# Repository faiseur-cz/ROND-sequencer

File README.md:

WARNING : It has been reported on modwiggler that this circuit is NOT OK!!! So please, check the forum. There were some solutions given. 
Right now i will not take the time needed to redo everything, because it would need some global redesign, and this project is not a priority for me.
Feel free to do it and write me directly or on the forum, it would be great!

Original description :
I finished the design and built a couple of them, all works as it should. So you can use the gerbers to make your own version.

There is a thread on modwiggler if you have any question :
https://modwiggler.com/forum/viewtopic.php?t=284588

ROND is an 8 step analog sequencer, kind of augmented (and circular!) baby8

- Pattern length rotary switch to set the number of steps in your sequence
- You can choose between two levels of CV (5v/2.5v), if you need more or less precision in the tuning of each step.
- Gates on/off for each step, on the right of the module.
- Run/Tune switch and Next Step push-button to facilitate tuning

CALIBRATION PROCEDURE :
- set the Run/Tune switch in TUNE position
- make sure the selected gate switch is ON (high position) and the corresponding pot is fully clockwise (maximum CV)
- monitor the CV output voltage and turn the trimpots until you reach precisely 5V (with the switch in 5V position) and 2.5V (with the switch in 2.5V position)
- DONE!

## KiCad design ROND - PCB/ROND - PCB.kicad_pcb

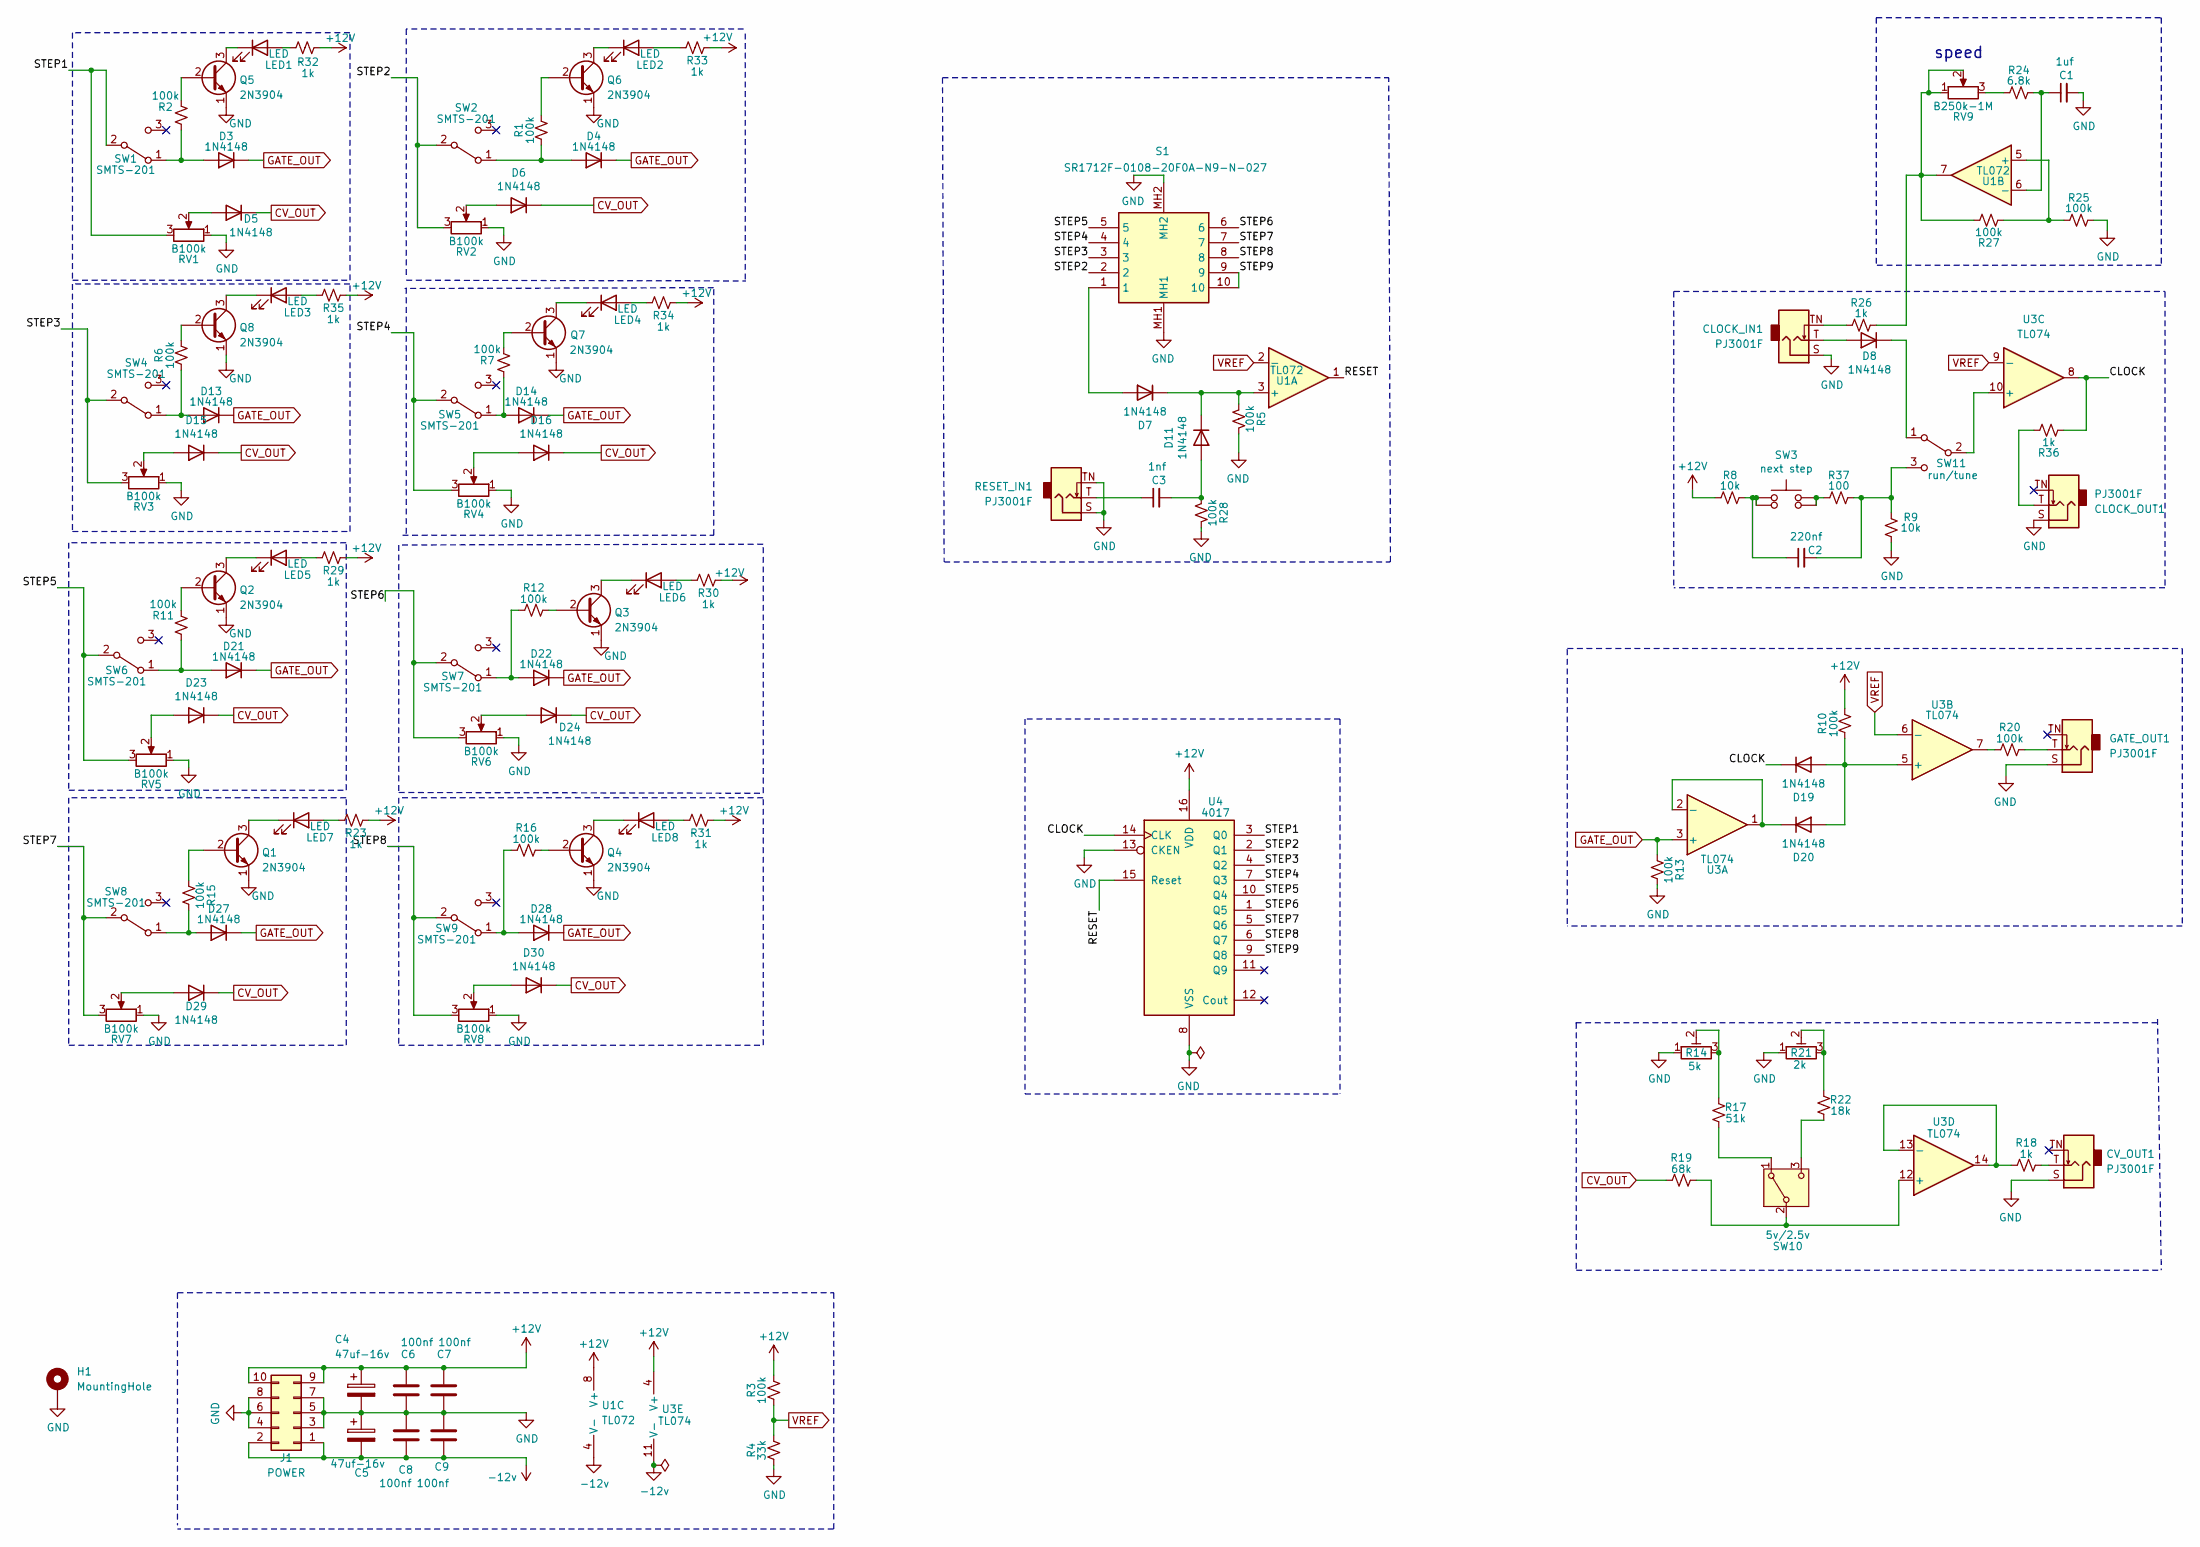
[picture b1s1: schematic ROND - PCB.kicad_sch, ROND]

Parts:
C1: 1uf; C_Rect_L7.2mm_W3.5mm_P5.00mm_FKS2_FKP2_MKS2_MKP2
C2: 220nf; C_Disc_D5.0mm_W2.5mm_P5.00mm
C3: 1nf; C_Rect_L7.2mm_W3.5mm_P5.00mm_FKS2_FKP2_MKS2_MKP2
C4, C5: 47uf-16v; CP_Radial_D5.0mm_P2.00mm
C6, C7, C8, C9: 100nf; C_Disc_D3.0mm_W2.0mm_P2.50mm
CLOCK_IN1: PJ3001F; Jack_3.5mm_QingPu_WQP-PJ398SM_Vertical_CircularHoles
CLOCK_OUT1: PJ3001F; Jack_3.5mm_QingPu_WQP-PJ398SM_Vertical_CircularHoles
CV_OUT1: PJ3001F; Jack_3.5mm_QingPu_WQP-PJ398SM_Vertical_CircularHoles
D3, D4, D5, D6, D7, D8, D11, D13, D14, D15, D16, D19, D20, D21, D22, D23, D24, D27, D28, D29, D30: 1N4148; D_DO-35_SOD27_P7.62mm_Horizontal
GATE_OUT1: PJ3001F; Jack_3.5mm_QingPu_WQP-PJ398SM_Vertical_CircularHoles
H1: MountingHole; MountingHole_3.2mm_M3_Pad_Via
J1: POWER; IDC-Header_2x05_P2.54mm_Vertical
LED1, LED2, LED3, LED4, LED5, LED6, LED7, LED8: LED; LED_D3.0mm
Q1, Q2, Q3, Q4, Q5, Q6, Q7, Q8: 2N3904; TO-92_Inline_Wide
R1, R2, R3, R5, R6, R7, R10, R11, R12, R13, R15, R16, R20, R25, R27, R28: 100k; R_Axial_DIN0207_L6.3mm_D2.5mm_P7.62mm_Horizontal
R4: 33k; R_Axial_DIN0207_L6.3mm_D2.5mm_P7.62mm_Horizontal
R8, R9: 10k; R_Axial_DIN0207_L6.3mm_D2.5mm_P7.62mm_Horizontal
R14: 5k; Potentiometer_Bourns_3296W_Vertical
R17: 51k; R_Axial_DIN0207_L6.3mm_D2.5mm_P7.62mm_Horizontal
R18, R23, R26, R29, R30, R31, R32, R33, R34, R35, R36: 1k; R_Axial_DIN0207_L6.3mm_D2.5mm_P7.62mm_Horizontal
R19: 68k; R_Axial_DIN0207_L6.3mm_D2.5mm_P7.62mm_Horizontal
R21: 2k; Potentiometer_Bourns_3296W_Vertical
R22: 18k; R_Axial_DIN0207_L6.3mm_D2.5mm_P7.62mm_Horizontal
R24: 6.8k; R_Axial_DIN0207_L6.3mm_D2.5mm_P7.62mm_Horizontal
R37: 100; R_Axial_DIN0207_L6.3mm_D2.5mm_P7.62mm_Horizontal
RESET_IN1: PJ3001F; Jack_3.5mm_QingPu_WQP-PJ398SM_Vertical_CircularHoles
RV1, RV2, RV3, RV4, RV5, RV6, RV7, RV8: B100k; Potentiometer_Alpha_RD901F-40-00D_Single_Vertical
RV9: B250k-1M; Potentiometer_Alpha_RD901F-40-00D_Single_Vertical
S1: SR1712F-0108-20F0A-N9-N-027; SR1712F010820F0AN9N027; Mouser Part Number 105-SR1712F-18NS
SW1, SW2, SW4, SW5, SW6, SW7, SW8, SW9: SMTS-201; SW_2MS1T1B1M2QES
SW3: next step; D6F90F1LFS
SW10: 5v/2.5v; SW_2MS1T1B1M2QES
SW11: run/tune; SW_2MS1T1B1M2QES
U1: TL072; DIP-8_W7.62mm_Socket
U3: TL074; DIP-14_W7.62mm_Socket
U4: 4017; DIP-16_W7.62mm_Socket

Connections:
+12V: C4.1, C6.1, C7.1, J1.9, J1.10, R3.1, R8.2, R10.1, R23.1, R29.1, R30.1, R31.1, R32.1, R33.1, R34.1, R35.1, U1.8 (V+), U3.4 (V+), U4.16 (VDD)
-12v: C5.2, C8.1, C9.1, J1.1, J1.2, U1.4 (V-), U3.11 (V-)
/CLOCK: D19.1 (K), R36.2, U3.8, U4.14 (CLK)
/RESET: U1.1, U4.15 (Reset)
/STEP1: RV1.3, SW1.2 (B), U4.3 (Q0)
/STEP2: RV2.3, S1.2, SW2.2 (B), U4.2 (Q1)
/STEP3: RV3.3, S1.3, SW4.2 (B), U4.4 (Q2)
/STEP4: RV4.3, S1.4, SW5.2 (B), U4.7 (Q3)
/STEP5: RV5.3, S1.5, SW6.2 (B), U4.10 (Q4)
/STEP6: RV6.3, S1.6, SW7.2 (B), U4.1 (Q5)
/STEP7: RV7.3, S1.7, SW8.2 (B), U4.5 (Q6)
/STEP8: RV8.3, S1.8, SW9.2 (B), U4.6 (Q7)
/STEP9: S1.9, S1.10, U4.9 (Q8)
CV_OUT: D5.1 (K), D6.1 (K), D15.1 (K), D16.1 (K), D23.1 (K), D24.1 (K), D29.1 (K), D30.1 (K), R19.2
GATE_OUT: D3.1 (K), D4.1 (K), D13.1 (K), D14.1 (K), D21.1 (K), D22.1 (K), D27.1 (K), D28.1 (K), R13.2, U3.3 (+)
GND: C1.2, C4.2, C5.1, C6.2, C7.2, C8.2, C9.2, CLOCK_IN1.S, CLOCK_OUT1.S, CV_OUT1.S, GATE_OUT1.S, H1.1, J1.3, J1.4, J1.5, J1.6, J1.7, J1.8, Q1.1 (E), Q2.1 (E), Q3.1 (E), Q4.1 (E), Q5.1 (E), Q6.1 (E), Q7.1 (E), Q8.1 (E), R4.2, R5.2, R9.1, R13.1, R14.1, R21.1, R25.1, R28.2, RESET_IN1.S, RESET_IN1.TN, RV1.1, RV2.1, RV3.1, RV4.1, RV5.1, RV6.1, RV7.1, RV8.1, S1.MH1, S1.MH2, U4.8 (VSS), U4.13 (CKEN)
unnamed: C2.1, R8.1, SW3.1, SW3.2
unnamed: C3.1, RESET_IN1.T
unnamed: CLOCK_IN1.TN, R26.2
unnamed: CLOCK_OUT1.T, R36.1
unnamed: CV_OUT1.T, R18.1
unnamed: D3.2 (A), R2.2, SW1.1 (A)
unnamed: D4.2 (A), R1.2, SW2.1 (A)
unnamed: D5.2 (A), RV1.2
unnamed: D6.2 (A), RV2.2
unnamed: D7.2 (A), S1.1
unnamed: CLOCK_IN1.T, D8.2 (A)
unnamed: D8.1 (K), SW11.1 (A)
unnamed: C3.2, D11.2 (A), R28.1
unnamed: D7.1 (K), D11.1 (K), R5.1, U1.3 (+)
unnamed: D13.2 (A), R6.2, SW4.1 (A)
unnamed: D14.2 (A), R7.2, SW5.1 (A)
unnamed: D15.2 (A), RV3.2
unnamed: D16.2 (A), RV4.2
unnamed: D19.2 (A), D20.2 (A), R10.2, U3.5 (+)
unnamed: D20.1 (K), U3.1, U3.2 (-)
unnamed: D21.2 (A), R11.2, SW6.1 (A)
unnamed: D22.2 (A), R12.2, SW7.1 (A)
unnamed: D23.2 (A), RV5.2
unnamed: D24.2 (A), RV6.2
unnamed: D27.2 (A), R15.1, SW8.1 (A)
unnamed: D28.2 (A), R16.2, SW9.1 (A)
unnamed: D29.2 (A), RV7.2
unnamed: D30.2 (A), RV8.2
unnamed: GATE_OUT1.T, R20.1
unnamed: LED1.2 (A), R32.2
unnamed: LED1.1 (K), Q5.3 (C)
unnamed: LED2.2 (A), R33.2
unnamed: LED2.1 (K), Q6.3 (C)
unnamed: LED3.2 (A), R35.2
unnamed: LED3.1 (K), Q8.3 (C)
unnamed: LED4.2 (A), R34.2
unnamed: LED4.1 (K), Q7.3 (C)
unnamed: LED5.2 (A), R29.2
unnamed: LED5.1 (K), Q2.3 (C)
unnamed: LED6.2 (A), R30.2
unnamed: LED6.1 (K), Q3.3 (C)
unnamed: LED7.2 (A), R23.2
unnamed: LED7.1 (K), Q1.3 (C)
unnamed: LED8.2 (A), R31.2
unnamed: LED8.1 (K), Q4.3 (C)
unnamed: Q1.2 (B), R15.2
unnamed: Q2.2 (B), R11.1
unnamed: Q3.2 (B), R12.1
unnamed: Q4.2 (B), R16.1
unnamed: Q5.2 (B), R2.1
unnamed: Q6.2 (B), R1.1
unnamed: Q7.2 (B), R7.1
unnamed: Q8.2 (B), R6.1
unnamed: R14.2, R14.3, R17.2
unnamed: R20.2, U3.7
unnamed: R21.2, R21.3, R22.2
unnamed: R24.2, RV9.3
unnamed: R26.1, R27.1, RV9.1, RV9.2, U1.7
unnamed: R37.2, SW3.3, SW3.4
unnamed: R17.1, SW10.1 (A)
unnamed: R19.1, SW10.2 (B), U3.12 (+)
unnamed: R22.1, SW10.3 (C)
unnamed: SW11.2 (B), U3.10 (+)
unnamed: C2.2, R9.2, R37.1, SW11.3 (C)
unnamed: R25.2, R27.2, U1.5 (+)
unnamed: C1.1, R24.1, U1.6 (-)
unnamed: R18.2, U3.13 (-), U3.14
VREF: R3.2, R4.1, U1.2 (-), U3.6 (-), U3.9 (-)

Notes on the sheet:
speed

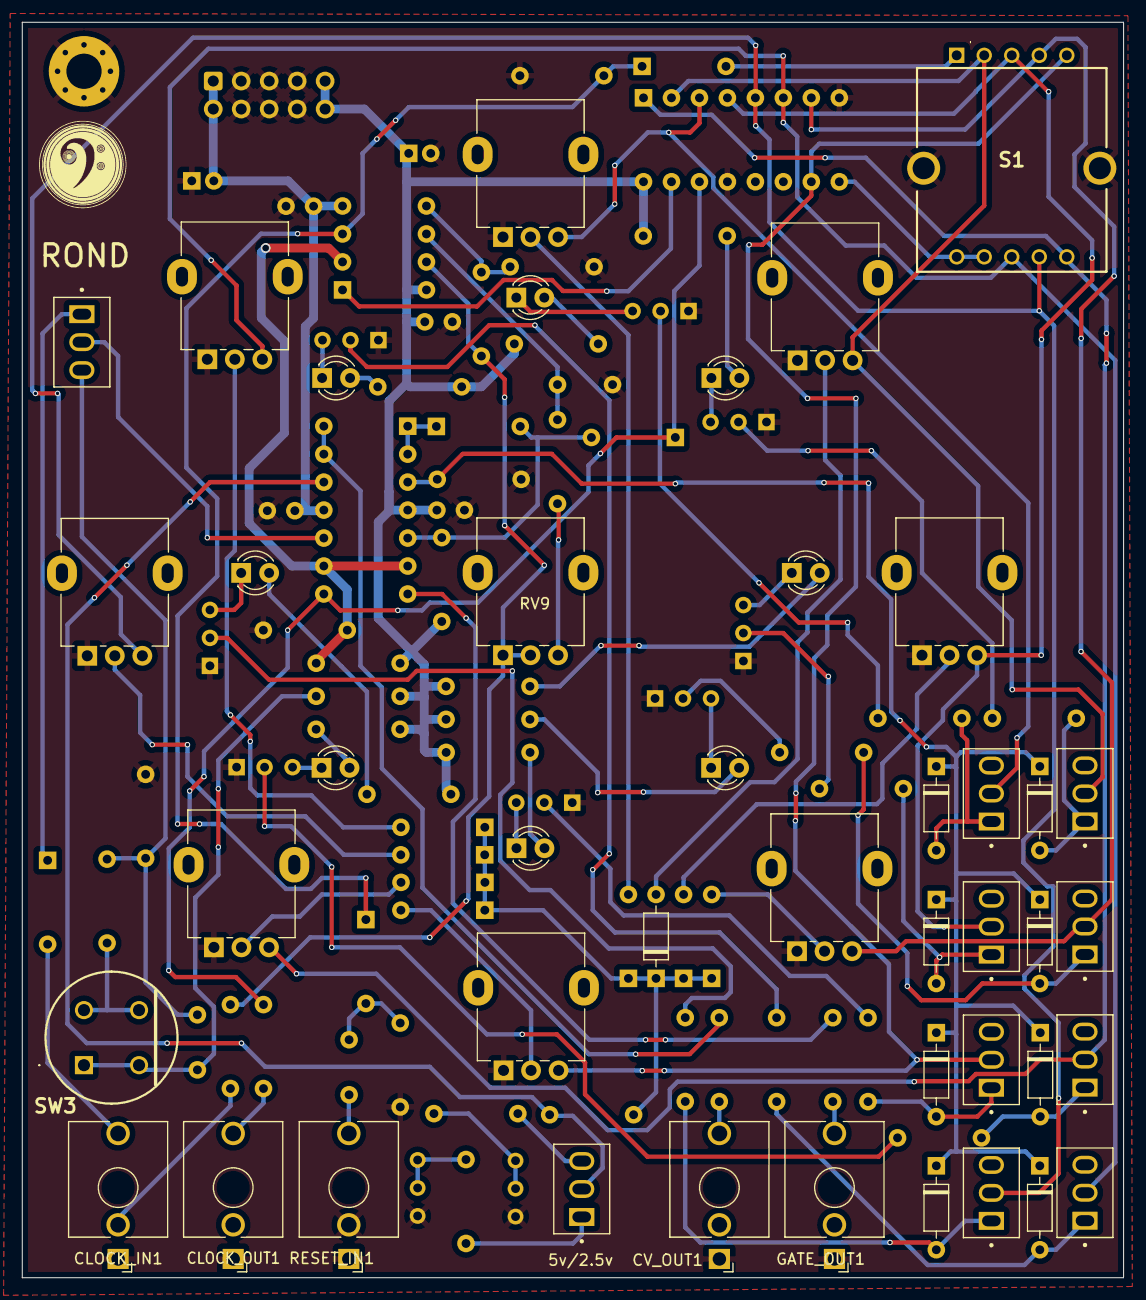
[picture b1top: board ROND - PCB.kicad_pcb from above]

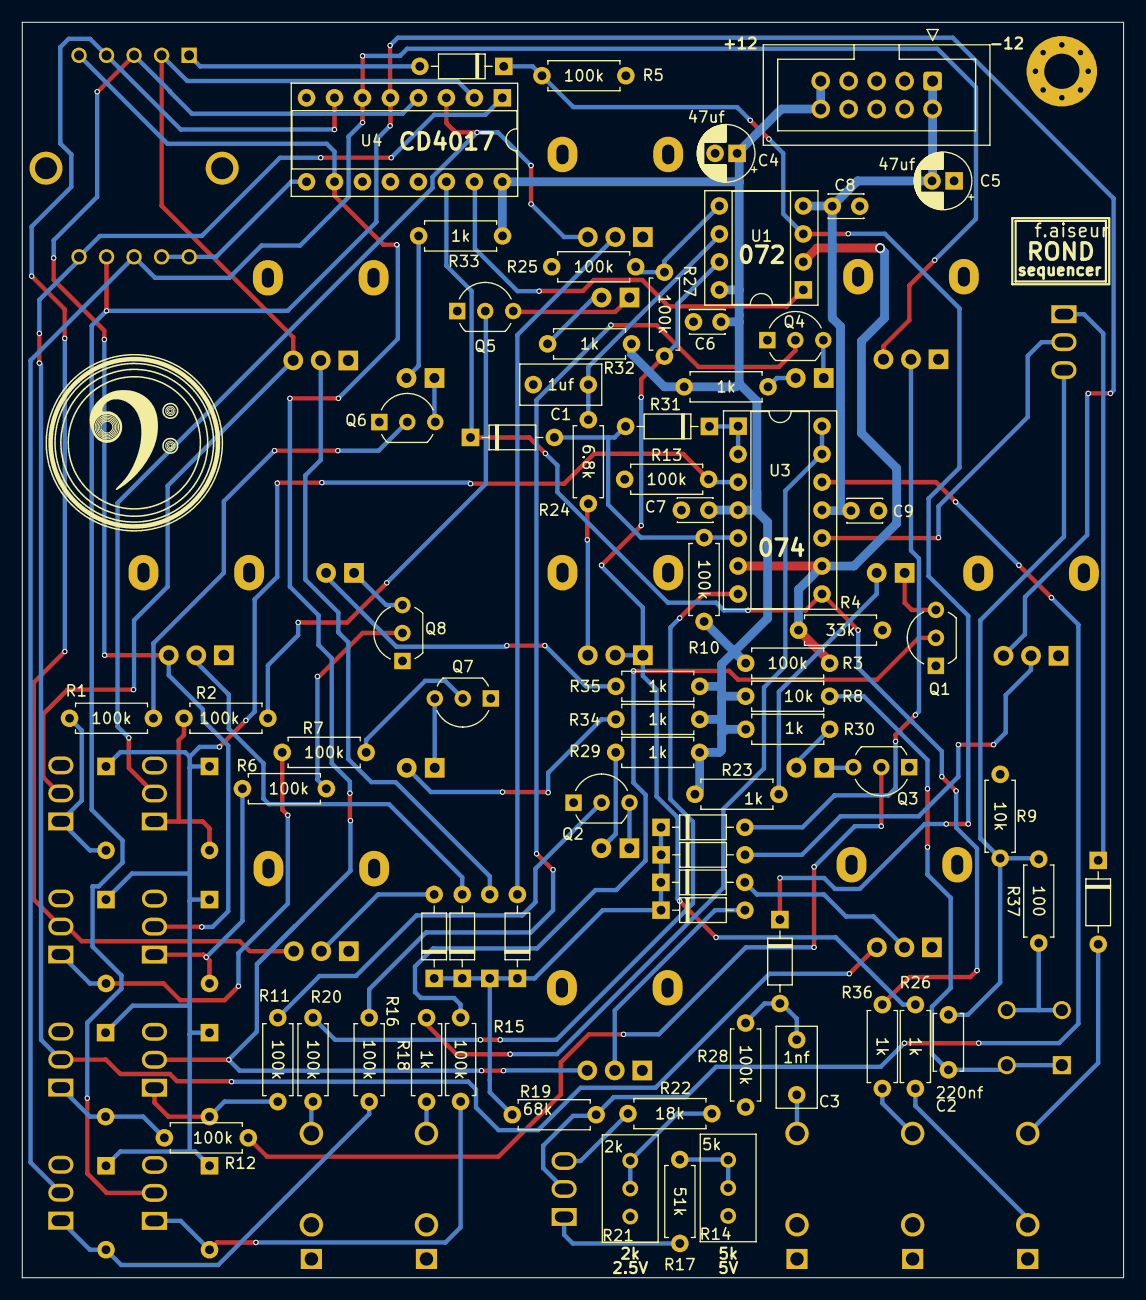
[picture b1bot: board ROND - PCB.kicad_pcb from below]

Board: 2 copper layers, 100.0 x 114.0 mm, 114 parts (70 on the bottom side), 84 nets.

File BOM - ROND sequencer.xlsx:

ROND SEQUENCER – BOM
Designator | Footprint | Qty | Designation | +++
DIODES/LED
LED6,LED5,LED1,LED2,LED3,LED8,LED4,LED7 | LED_D3.0mm | 8 | LED
D28,D14,D21,D27,D13,D4,D3,D22,D23,D5, D15,D6,D7,D20,D29,D8,D11,D24,D19,D30,D16 | D_DO-35_SOD27_P7.62mm_Horizontal | 21 | 1N4148
JACKS
RESET_IN1,CLOCK_IN1,GATE_OUT1, CV_OUT1,CLOCK_OUT1 | Jack_3.5mm | 5 | Jacks
SWITCHES
SW10 | SW_2MS1T1B1M2QES | 1 | 5v/2.5v | SMTS-102-A2
SW1,SW7,SW4,SW9,SW2,SW6,SW5,SW8 | SW_2MS1T1B1M2QES | 8 | SMTS-201 | SMTS-102-A2
SW11 | SW_2MS1T1B1M2QES | 1 | run/tune | SMTS-102-A2
S1 | SR1712F010820F0AN9N027 | 1 | Rotary Switch 1P8T
SW3 | D6F90F1LFS | 1 | next step Push Switch
TRANSISTORS
Q4,Q7,Q3,Q2,Q1,Q8,Q6,Q5 | TO-92_Inline_Wide | 8 | 2N3904
CAPACITORS
C5,C4 | CP_Radial_D5.0mm_P2.00mm | 2 | 47uf | POLARIZED
C3 | C_Rect_L7.2mm_W3.5mm_P5.00mm | 1 | 1nf | FILM
C2 | C_Disc_D5.0mm_W2.5mm_P5.00mm | 1 | 220nf | CERAMIC
C1 | C_Rect_L7.2mm_W3.5mm_P5.00mm | 1 | 1uf | FILM
C7,C9,C8,C6 | C_Disc_D3.0mm_W2.0mm_P2.50mm | 4 | 100nf | CERAMIC
RESISTORS
R12,R5,R10,R2,R3,R13,R16,R20,R6,R1, R7,R15,R11,R28,R27,R25 | R_Axial_DIN0207_L6.3mm_D2.5mm_P7.62mm_Horizontal | 16 | 100k
R24 | R_Axial_DIN0207_L6.3mm_D2.5mm_P7.62mm_Horizontal | 1 | 6.8k
R29,R36,R34,R33,R30,R35,R32,R31,R18,R26,R23 | R_Axial_DIN0207_L6.3mm_D2.5mm_P7.62mm_Horizontal | 11 | 1k
R9,R8 | R_Axial_DIN0207_L6.3mm_D2.5mm_P7.62mm_Horizontal | 2 | 10k
R19 | R_Axial_DIN0207_L6.3mm_D2.5mm_P7.62mm_Horizontal | 1 | 68k
R4 | R_Axial_DIN0207_L6.3mm_D2.5mm_P7.62mm_Horizontal | 1 | 33k
R17 | R_Axial_DIN0207_L6.3mm_D2.5mm_P7.62mm_Horizontal | 1 | 51k
R22 | R_Axial_DIN0207_L6.3mm_D2.5mm_P7.62mm_Horizontal | 1 | 18k
R37 | R_Axial_DIN0207_L6.3mm_D2.5mm_P7.62mm_Horizontal | 1 | 100
POTENTIOMETERS
RV8,RV2,RV6,RV5,RV4,RV7,RV3,RV1 | Potentiometer_Alpha_RD901F-40-00D_Single_Vertical | 8 | B100k
RV9 | Potentiometer_Alpha_RD901F-40-00D_Single_Vertical | 1 | B250k-1M
TRIMMERS
R14 | Bourns_3296W_Vertical | 1 | 5k
R21 | Bourns_3296W_Vertical | 1 | 2k
MISC
J1 | IDC-Header_2x05_P2.54mm_Vertical | 1 | POWER
U1 | DIP-8_W7.62mm_Socket | 1 | TL072
U3 | DIP-14_W7.62mm_Socket | 1 | TL074
U4 | DIP-16_W7.62mm_Socket | 1 | 4017

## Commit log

2025-04-17 IMPORTANT Update README.md
